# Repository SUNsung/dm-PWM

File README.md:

Many modules for building a multi-channel downmix PWM controller

Central control unit:
Coming soon ...

PWM controller module with driver:

Main characteristics:
 - logic level: 12V
 - working load: up to 10A
 - maximum load: 25A

Implemented by:
- dual position indicator of the driver;
- control of input voltage;
- control of the output voltage;
- temperature control on the thermistor;
- set the RC filter at the output;
- output of the external cooler control from the logic level power supply bus;

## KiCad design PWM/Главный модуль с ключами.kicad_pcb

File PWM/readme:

PWM controller module on mosfet with driver.
  
  Main characteristics:
  - logic level: 12V
  - working load: up to 10A
  - maximum load: 25A

Implemented by:
- dual position indicator of the driver;
- control of input voltage;
- control of the output voltage;
- temperature control on the thermistor;
- set the RC filter at the output;
- output of the external cooler control from the logic level power supply bus;

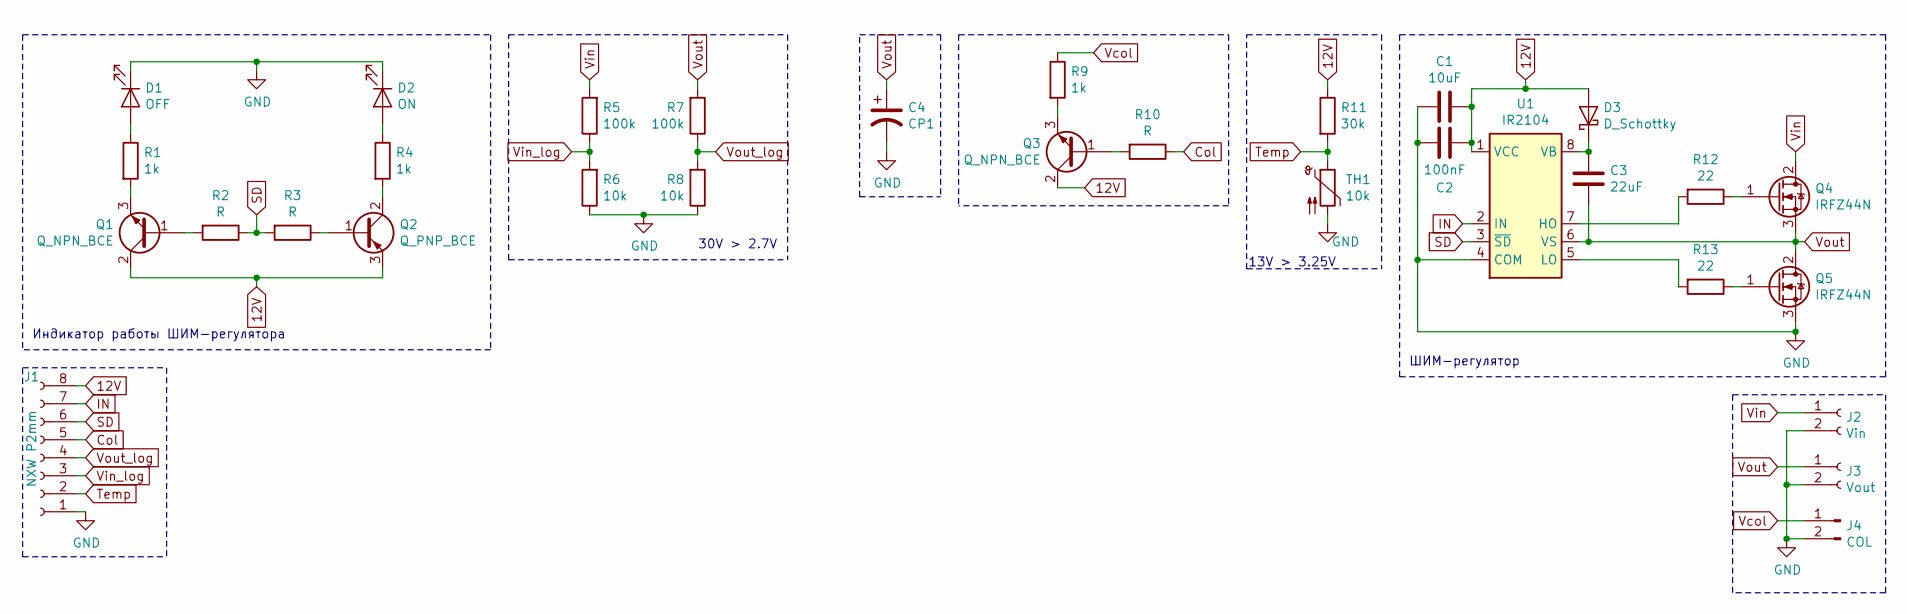
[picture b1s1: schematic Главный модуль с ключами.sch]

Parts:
C1: 10uF; C_0805_2012Metric
C2: 100nF; C_0805_2012Metric
C3: 22uF; C_0805_2012Metric
C4: CP1; CP_Radial_D10.0mm_P2.50mm_P5.00mm
D1: OFF; D_0805_2012Metric
D2: ON; D_0805_2012Metric
D3: D_Schottky; D_SMA
J1: NXW P2mm; PinHeader_1x08_P2.00mm_Vertical
J2: Vin; PhoenixContact_MCV_1,5_2-G-5.08_1x02_P5.08mm_Vertical
J3: Vout; PhoenixContact_MCV_1,5_2-G-5.08_1x02_P5.08mm_Vertical
J4: COL; PinSocket_1x02_P2.54mm_Vertical
Q1, Q3: Q_NPN_BCE; SOT-23
Q2: Q_PNP_BCE; SOT-23
Q4, Q5: IRFZ44N; TO-220-IRFZ44-DWN
R1, R4, R9: 1k; R_0805_2012Metric
R2, R3, R10: R; R_0805_2012Metric
R5, R7: 100k; R_0805_2012Metric
R6, R8: 10k; R_0805_2012Metric
R11: 30k; R_0805_2012Metric
R12, R13: 22; R_0805_2012Metric
TH1: 10k; R_0805_2012Metric
U1: IR2104; SOIC-8_3.9x4.9mm_P1.27mm

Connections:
12V: C1.2, C2.1, D3.2 (A), J1.8, Q1.2 (C), Q2.3 (E), Q3.2 (C), R11.1, U1.1 (VCC)
Col: J1.5, R10.1
GND: C1.1, C2.2, C4.2, D1.1 (K), D2.1 (K), J1.1, J2.2, J3.2, J4.2, Q5.3 (S), R6.1, R8.1, TH1.2, U1.4 (COM)
IN: J1.7, U1.2 (IN)
unnamed: C3.2, D3.1 (K), U1.8 (VB)
unnamed: D1.2 (A), R1.1
unnamed: D2.2 (A), R4.1
unnamed: Q1.1 (B), R2.2
unnamed: Q1.3 (E), R1.2
unnamed: Q2.1 (B), R3.1
unnamed: Q2.2 (C), R4.2
unnamed: Q3.1 (B), R10.2
unnamed: Q3.3 (E), R9.2
unnamed: Q4.1 (G), R12.1
unnamed: Q5.1 (G), R13.1
unnamed: R12.2, U1.7 (HO)
unnamed: R13.2, U1.5 (LO)
SD: J1.6, R2.1, R3.2, U1.3 (~SD)
Temp: J1.2, R11.2, TH1.1
Vcol: J4.1, R9.1
Vin: J2.1, Q4.2 (D), R5.2
Vin_log: J1.3, R5.1, R6.2
Vout: C3.1, C4.1, J3.1, Q4.3 (S), Q5.2 (D), R7.2, U1.6 (VS)
Vout_log: J1.4, R7.1, R8.2

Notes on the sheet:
Индикатор работы ШИМ-регулятора
ШИМ-регулятор
30V > 2.7V
13V > 3.25V

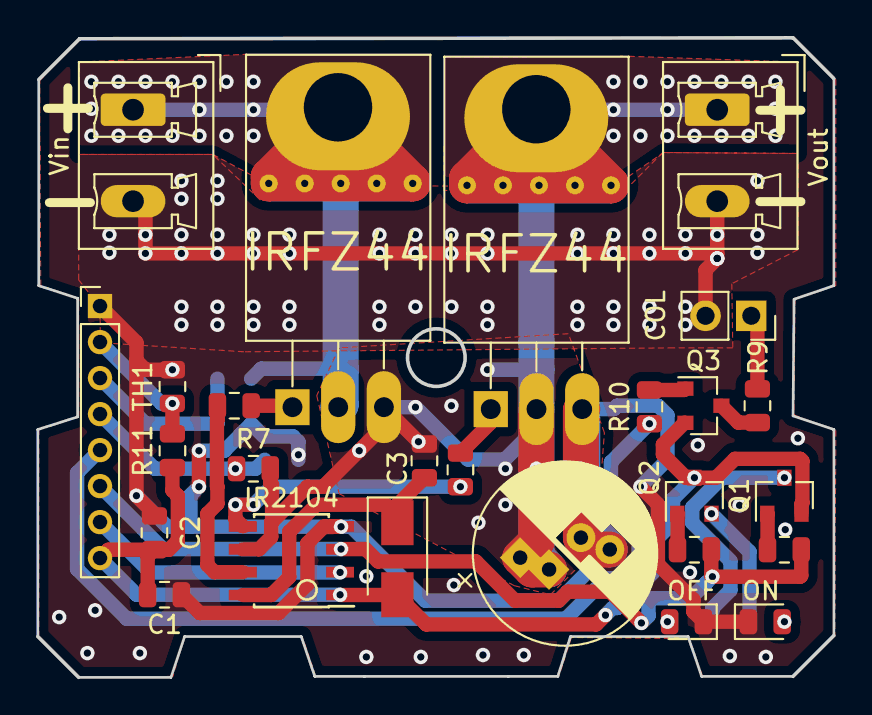
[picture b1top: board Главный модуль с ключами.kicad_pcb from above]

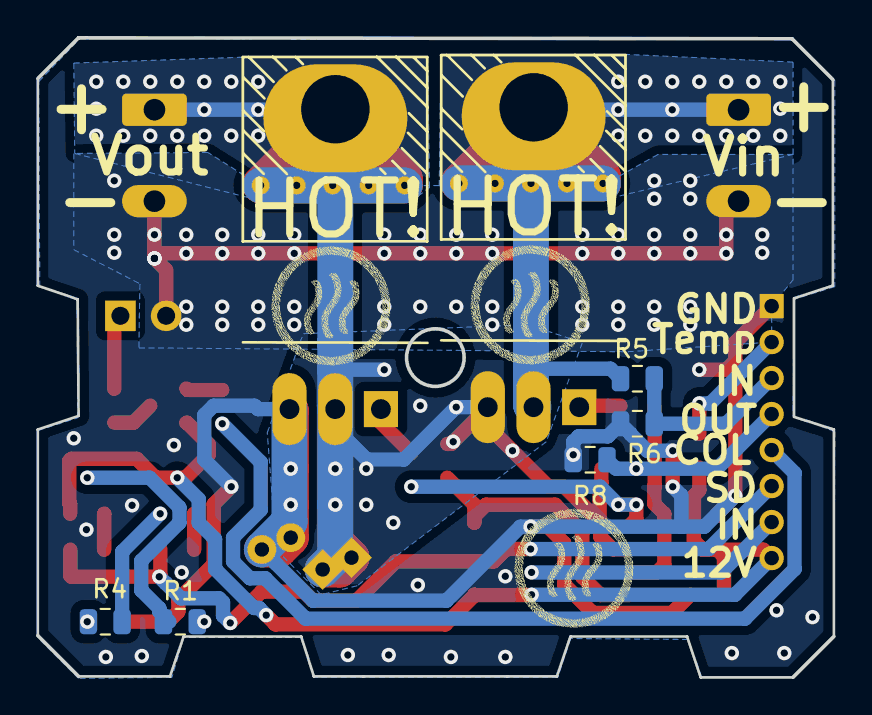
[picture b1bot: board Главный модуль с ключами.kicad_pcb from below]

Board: 2 copper layers, 44.2 x 35.5 mm, 31 parts (5 on the bottom side), 24 nets.
